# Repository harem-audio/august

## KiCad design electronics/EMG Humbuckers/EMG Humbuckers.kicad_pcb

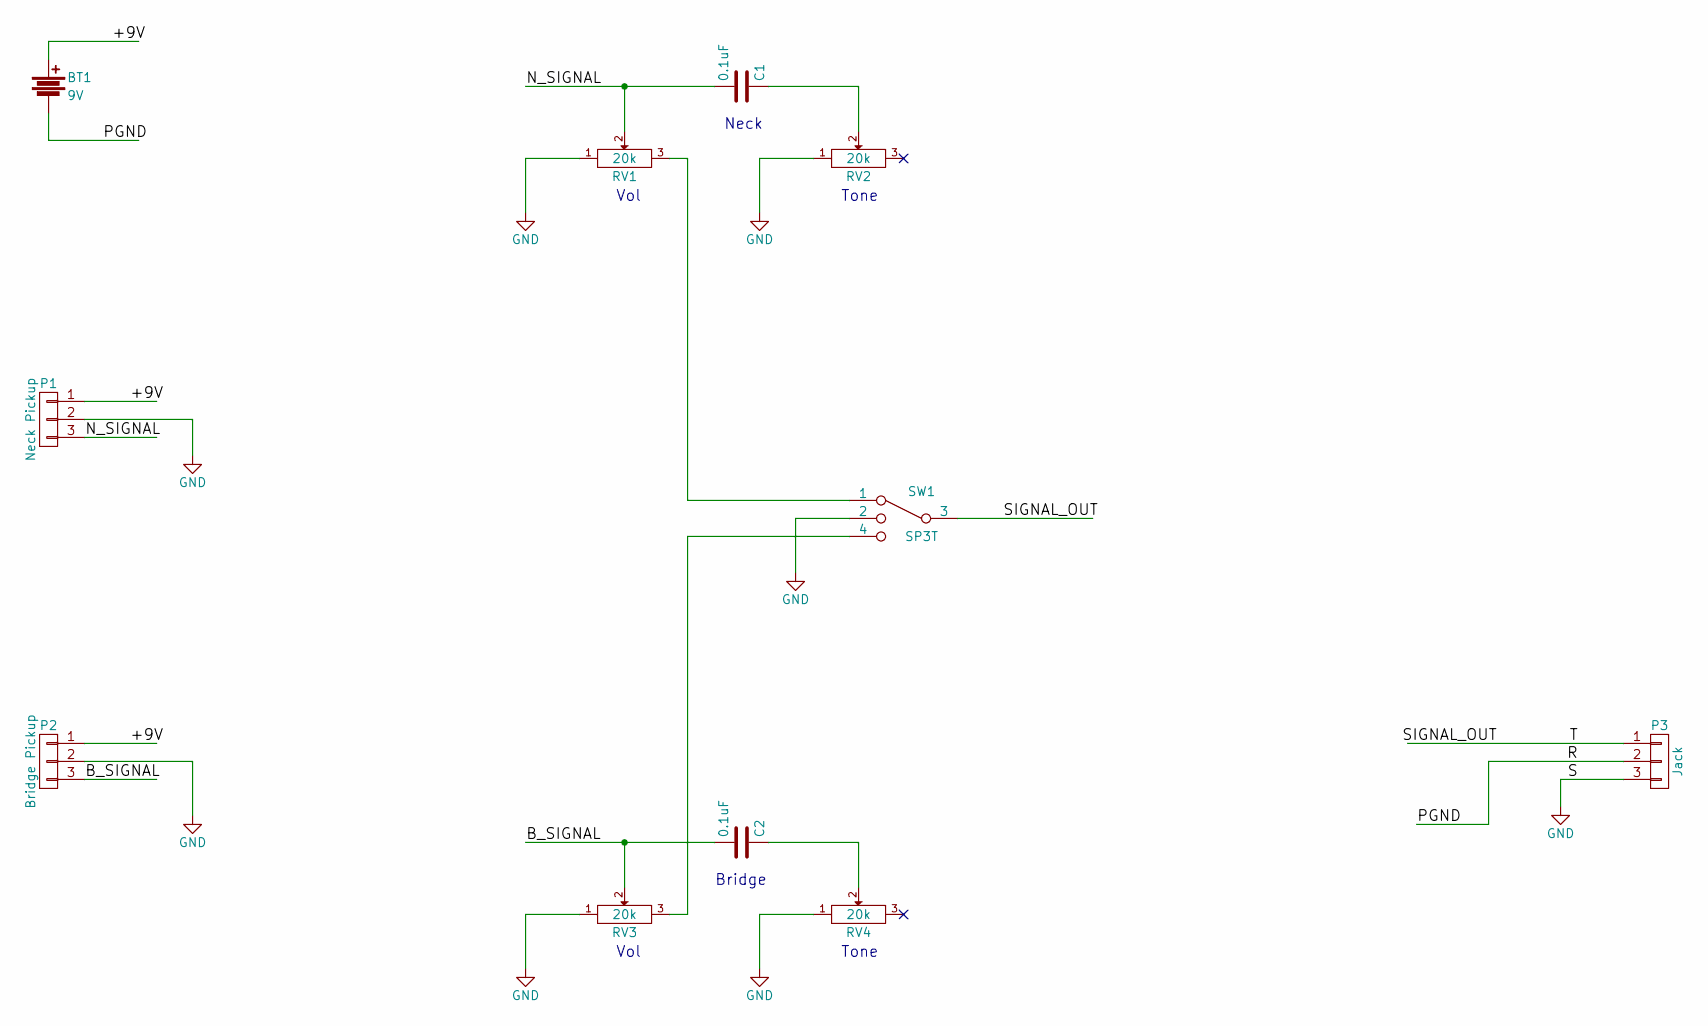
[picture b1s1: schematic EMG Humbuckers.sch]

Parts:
BT1: 9V; 9V-1294
C1, C2: 0.1uF; C_1206_HandSoldering
P1: Neck Pickup; Pin_Header_Straight_1x03
P2: Bridge Pickup; Pin_Header_Straight_1x03
P3: Jack; Pin_Header_Straight_1x03
RV1, RV2, RV3, RV4: 20k; Bourns-PVT09
SW1: SP3T; Pin_Header_Straight_1x04

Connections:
/+9V: BT1.1, P1.1, P2.1
/B_SIGNAL: C2.2, P2.3, RV3.2
/N_SIGNAL: C1.2, P1.3, RV1.2
/PGND: BT1.2, P3.2
/SIGNAL_OUT: P3.1, SW1.3
GND: P1.2, P2.2, P3.3, RV1.1, RV2.1, RV3.1, RV4.1, SW1.2
unnamed: C1.1, RV2.2
unnamed: C2.1, RV4.2
unnamed: RV1.3, SW1.1
unnamed: RV3.3, SW1.4

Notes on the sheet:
Bridge
Neck
Vol
Tone

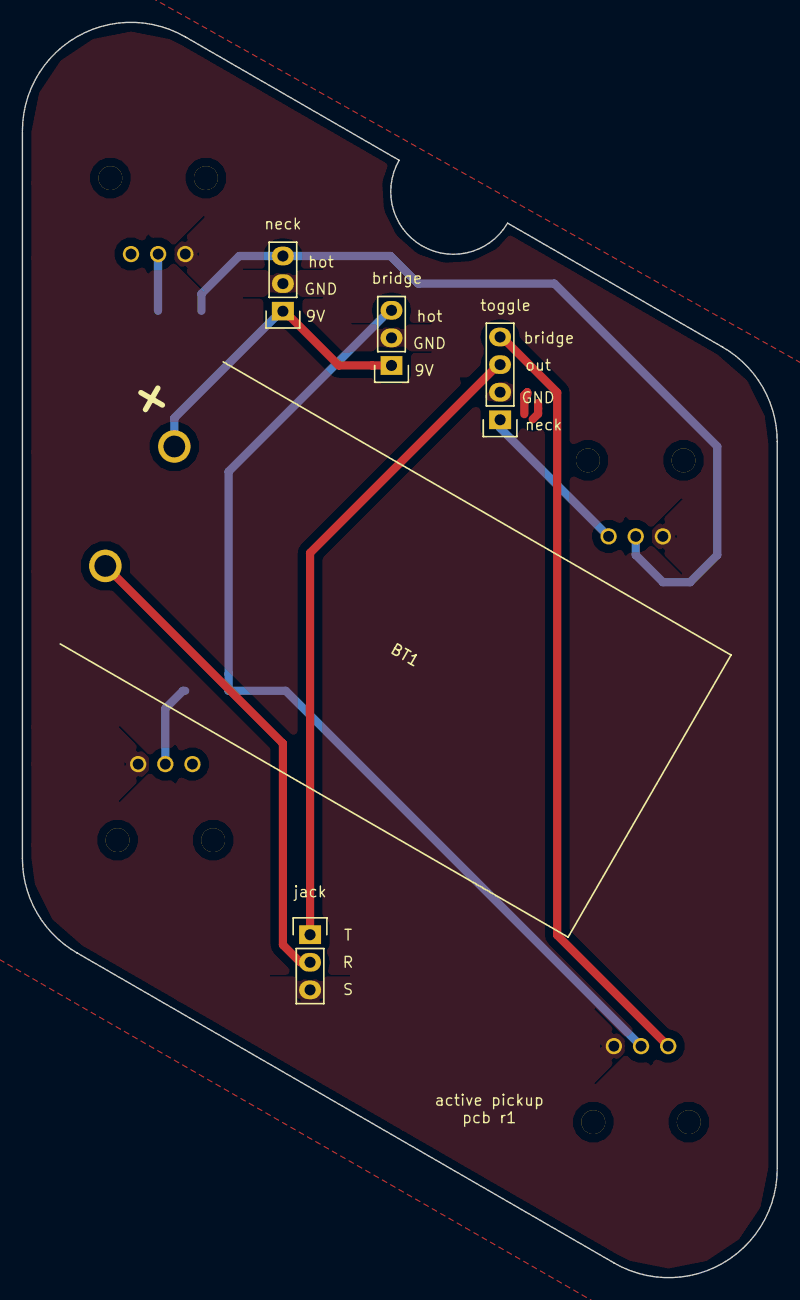
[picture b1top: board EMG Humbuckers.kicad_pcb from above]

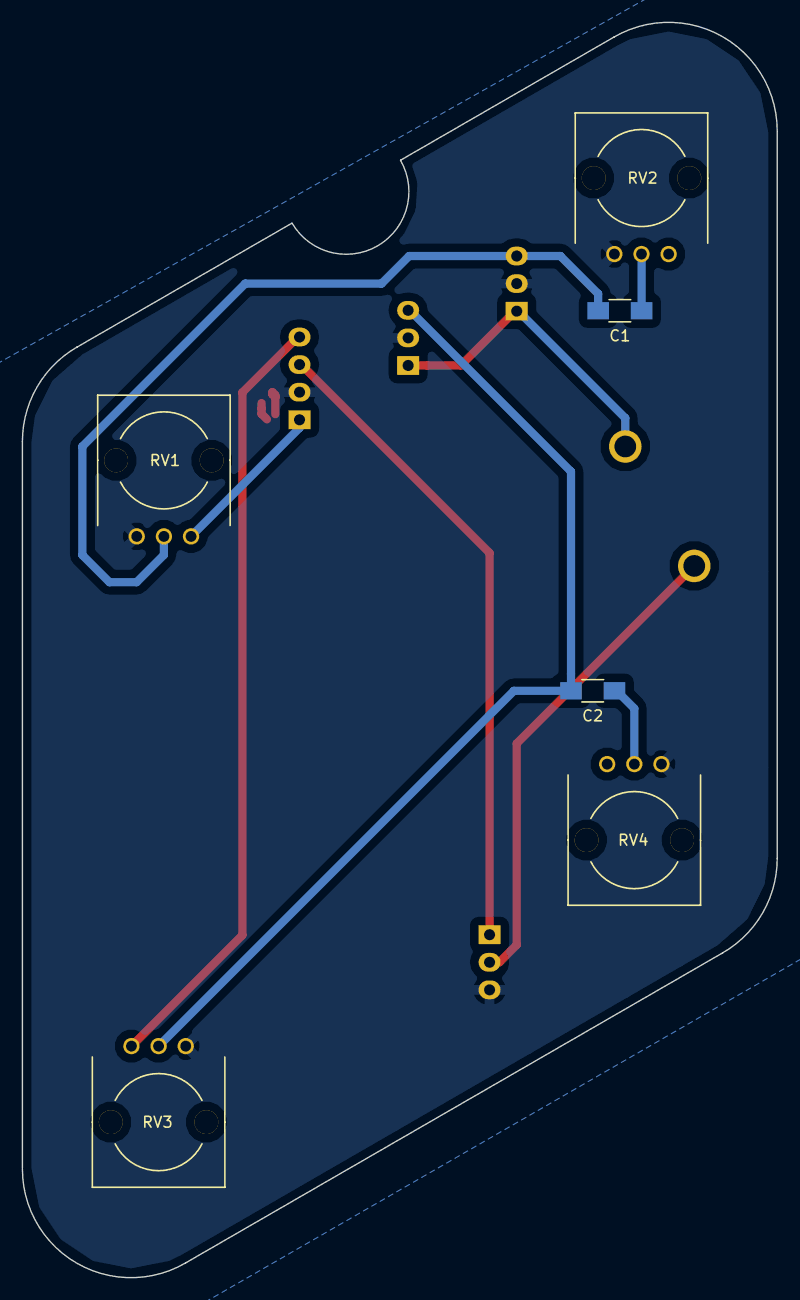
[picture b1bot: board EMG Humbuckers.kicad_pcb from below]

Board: 2 copper layers, 69.5 x 115.6 mm, 11 parts (6 on the bottom side), 10 nets.

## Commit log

2016-02-23 init
2016-02-23 add CAD stuff
